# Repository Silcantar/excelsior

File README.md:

# *Excelsior*
>
>Tentative layout and design for *Excelsior*.

*Excelsior* is a 150% (153 keys) 3-section hand-wired keyboard (optionally) using uniform keycaps in a curved plate.

The main section is based on a standard ANSI 60% keyboard, but with a row of 15 function/programmable-macro keys at the top and 5 keys below the 7u spacebar.

The peripheral sections are each 6x6 ortholinear boards and can be placed on either side of the main section, including placing both on the same side of the main. They are connected to the main section by 20-pin pogo pin connectors either directly or via a custom cable. In the default keymap one section is an extended numpad and the other is a large navigation/macro pad. The top row of each peripheral is dedicated to additional function/programmable-macro keys for a total of 27.

The microcontroller is a Pimoroni PGA2350 board located in the main section. The matrix for the main section is wired directly to the controller board, while the I/O for the peripheral sections is handled by an MCP23017 I/O expander in each section communicating with the controller via I²C. The connections between the sections carry the signals necessary for both I²C and for SPI, plus several spare lines for interrupts, chip selects, or other I/O.

The matrix of the main section also has a seventh row that can be used for up to 14 momentary, toggle, or rotary switches on the top bezel of the keyboard. Note that the keys below the spacebar are on the sixth (spacebar) row of the matrix, so the seventh row is completely open.

Because of the massive number of GPIO pins on the PGA2350 and the I/O expanders, there is ample spare I/O for any functionality you could possibly want, from displays, encoders, LEDs, etc.

Because QMK does not currently support the RP2350 or displays larger than 128×64, I am planning to use KMK for the firmware.

For those interested, I have designed a [custom set](https://yuzukeycaps.com/c/4633754e-42e4-428c-9306-6221ce11477c)[^1] of KAM keycaps with a white-on-black-with-blue-accents *Wall Street Journal*-inspired aesthetic for *Excelsior* at YUZU Keycaps. They also feature secondary legends for a Greek alphabet/symbol layer and the macro keys are labeled with Greek numerals. There are a number of extra keys for alternative layouts too. Since the keycaps have a uniform profile any key can be placed on any row.

[^1]: If the link does not work, you can import [this JSON file](keycaps/Excelsior.json) to YUZU

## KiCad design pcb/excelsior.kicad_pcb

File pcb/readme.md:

This is a hand-wired build, so the "PCBs" here are not meant for production. I am using them to select and record the necessary components and to verify that the wiring topology is feasible.

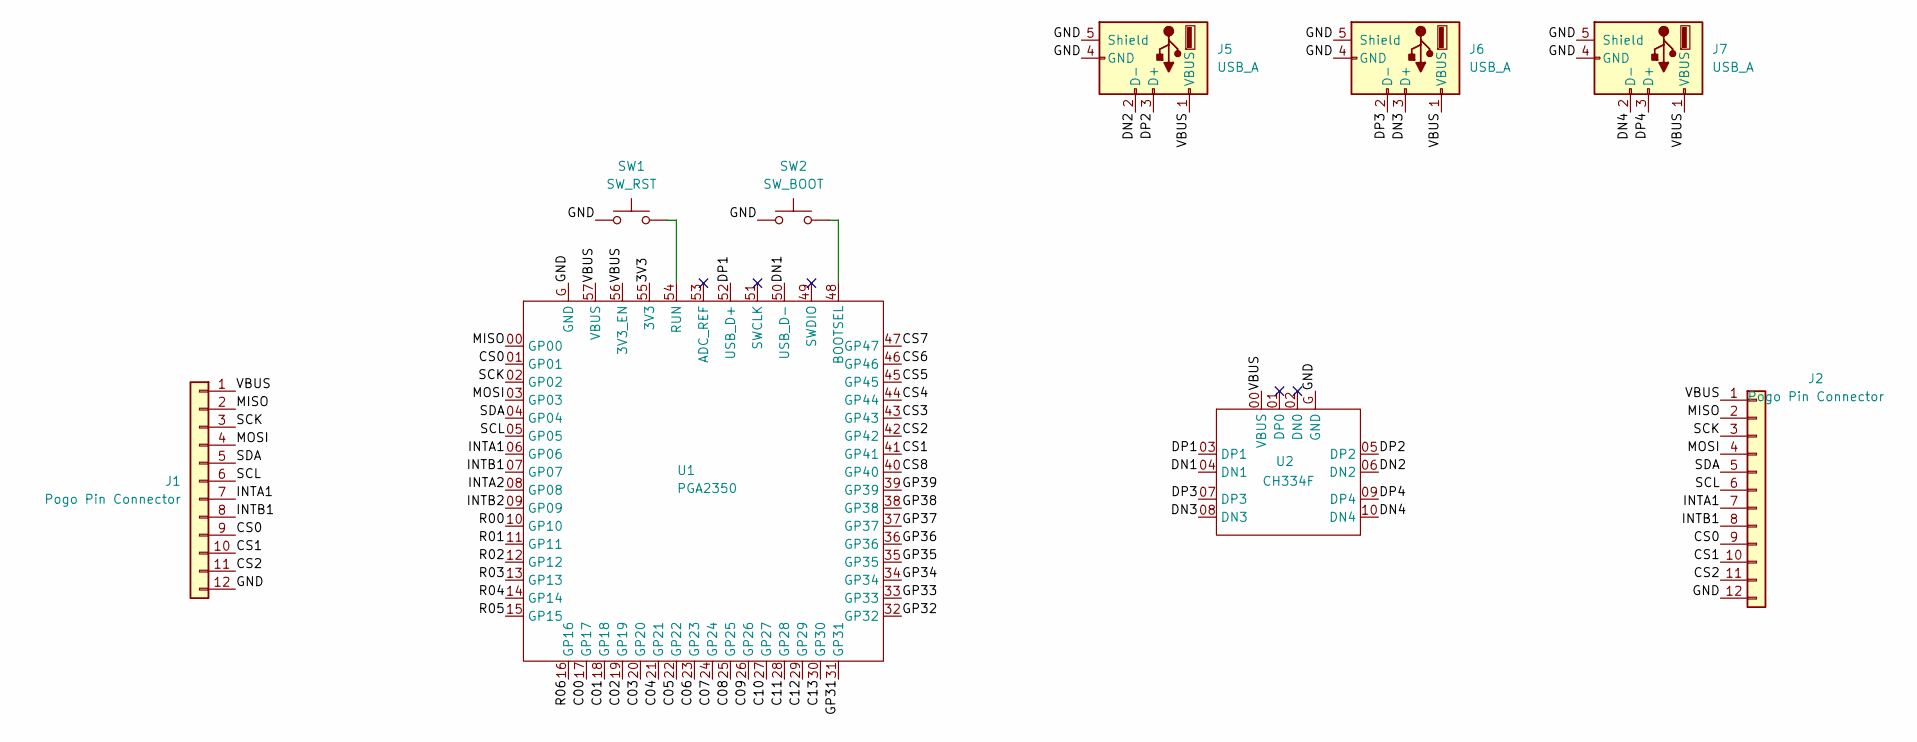
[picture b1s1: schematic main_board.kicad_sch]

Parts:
J1, J2: Pogo Pin Connector; PinHeader_1x12_P2.54mm_Vertical
J5, J6, J7: USB_A; USB_A_Molex_67643_Horizontal
SW1: SW_RST; SW_PUSH_6mm
SW2: SW_BOOT; SW_PUSH_6mm
U1: PGA2350
U2: CH334F; USB_Hub

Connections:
/Main Board/3V3: U1.55 (3V3)
/Main Board/C00: U1.17 (GP17)
/Main Board/C01: U1.18 (GP18)
/Main Board/C02: U1.19 (GP19)
/Main Board/C03: U1.20 (GP20)
/Main Board/C04: U1.21 (GP21)
/Main Board/C05: U1.22 (GP22)
/Main Board/C06: U1.23 (GP23)
/Main Board/C07: U1.24 (GP24)
/Main Board/C08: U1.25 (GP25)
/Main Board/C09: U1.26 (GP26)
/Main Board/C10: U1.27 (GP27)
/Main Board/C11: U1.28 (GP28)
/Main Board/C12: U1.29 (GP29)
/Main Board/C13: U1.30 (GP30)
/Main Board/CS0: J1.9, J2.9, U1.01 (GP01)
/Main Board/CS1: J1.10, J2.10, U1.41 (GP41)
/Main Board/CS2: J1.11, J2.11, U1.42 (GP42)
/Main Board/CS3: U1.43 (GP43)
/Main Board/CS4: U1.44 (GP44)
/Main Board/CS5: U1.45 (GP45)
/Main Board/CS6: U1.46 (GP46)
/Main Board/CS7: U1.47 (GP47)
/Main Board/CS8: U1.40 (GP40)
/Main Board/DN1: U1.50 (USB_D-), U2.04 (DN1)
/Main Board/DN2: J5.2 (D-), U2.06 (DN2)
/Main Board/DN3: J6.3 (D+), U2.08 (DN3)
/Main Board/DN4: J7.2 (D-), U2.10 (DN4)
/Main Board/DP1: U1.52 (USB_D+), U2.03 (DP1)
/Main Board/DP2: J5.3 (D+), U2.05 (DP2)
/Main Board/DP3: J6.2 (D-), U2.07 (DP3)
/Main Board/DP4: J7.3 (D+), U2.09 (DP4)
/Main Board/GND: J1.12, J2.12, J5.4 (GND), J5.5 (Shield), J6.4 (GND), J6.5 (Shield), J7.4 (GND), J7.5 (Shield), SW1.1, SW2.1, U1.G (GND), U2.G (GND)
/Main Board/GP31: U1.31 (GP31)
/Main Board/GP32: U1.32 (GP32)
/Main Board/GP33: U1.33 (GP33)
/Main Board/GP34: U1.34 (GP34)
/Main Board/GP35: U1.35 (GP35)
/Main Board/GP36: U1.36 (GP36)
/Main Board/GP37: U1.37 (GP37)
/Main Board/GP38: U1.38 (GP38)
/Main Board/GP39: U1.39 (GP39)
/Main Board/INTA1: J1.7, J2.7, U1.06 (GP06)
/Main Board/INTA2: U1.08 (GP08)
/Main Board/INTB1: J1.8, J2.8, U1.07 (GP07)
/Main Board/INTB2: U1.09 (GP09)
/Main Board/MISO: J1.2, J2.2, U1.00 (GP00)
/Main Board/MOSI: J1.4, J2.4, U1.03 (GP03)
/Main Board/R00: U1.10 (GP10)
/Main Board/R01: U1.11 (GP11)
/Main Board/R02: U1.12 (GP12)
/Main Board/R03: U1.13 (GP13)
/Main Board/R04: U1.14 (GP14)
/Main Board/R05: U1.15 (GP15)
/Main Board/R06: U1.16 (GP16)
/Main Board/SCK: J1.3, J2.3, U1.02 (GP02)
/Main Board/SCL: J1.6, J2.6, U1.05 (GP05)
/Main Board/SDA: J1.5, J2.5, U1.04 (GP04)
/Main Board/VBUS: J1.1, J2.1, J5.1 (VBUS), J6.1 (VBUS), J7.1 (VBUS), U1.56 (3V3_EN), U1.57 (VBUS), U2.00 (VBUS)
unnamed: SW2.2, U1.48 (BOOTSEL)
unnamed: SW1.2, U1.54 (RUN)

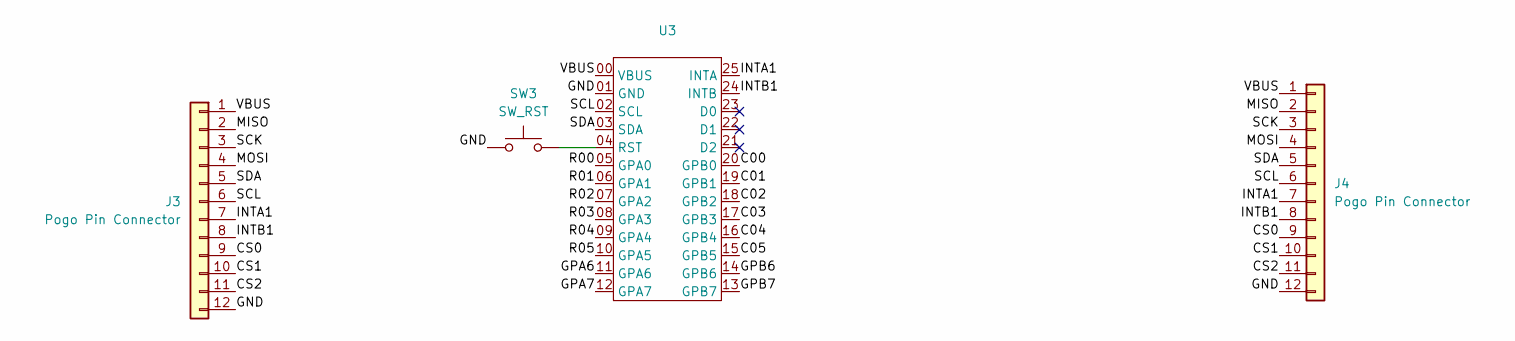
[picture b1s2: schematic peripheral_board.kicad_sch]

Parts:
J3, J4: Pogo Pin Connector; PinHeader_1x12_P2.54mm_Vertical
SW3: SW_RST; SW_PUSH_6mm
U3: MCP23017_Breakout

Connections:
/Peripheral Board/C00: U3.20 (GPB0)
/Peripheral Board/C01: U3.19 (GPB1)
/Peripheral Board/C02: U3.18 (GPB2)
/Peripheral Board/C03: U3.17 (GPB3)
/Peripheral Board/C04: U3.16 (GPB4)
/Peripheral Board/C05: U3.15 (GPB5)
/Peripheral Board/CS0: J3.9, J4.9
/Peripheral Board/CS1: J3.10, J4.10
/Peripheral Board/CS2: J3.11, J4.11
/Peripheral Board/GND: J3.12, J4.12, SW3.1, U3.01 (GND)
/Peripheral Board/GPA6: U3.11 (GPA6)
/Peripheral Board/GPA7: U3.12 (GPA7)
/Peripheral Board/GPB6: U3.14 (GPB6)
/Peripheral Board/GPB7: U3.13 (GPB7)
/Peripheral Board/INTA1: J3.7, J4.7, U3.25 (INTA)
/Peripheral Board/INTB1: J3.8, J4.8, U3.24 (INTB)
/Peripheral Board/MISO: J3.2, J4.2
/Peripheral Board/MOSI: J3.4, J4.4
/Peripheral Board/R00: U3.05 (GPA0)
/Peripheral Board/R01: U3.06 (GPA1)
/Peripheral Board/R02: U3.07 (GPA2)
/Peripheral Board/R03: U3.08 (GPA3)
/Peripheral Board/R04: U3.09 (GPA4)
/Peripheral Board/R05: U3.10 (GPA5)
/Peripheral Board/SCK: J3.3, J4.3
/Peripheral Board/SCL: J3.6, J4.6, U3.02 (SCL)
/Peripheral Board/SDA: J3.5, J4.5, U3.03 (SDA)
/Peripheral Board/VBUS: J3.1, J4.1, U3.00 (VBUS)
unnamed: SW3.2, U3.04 (RST)

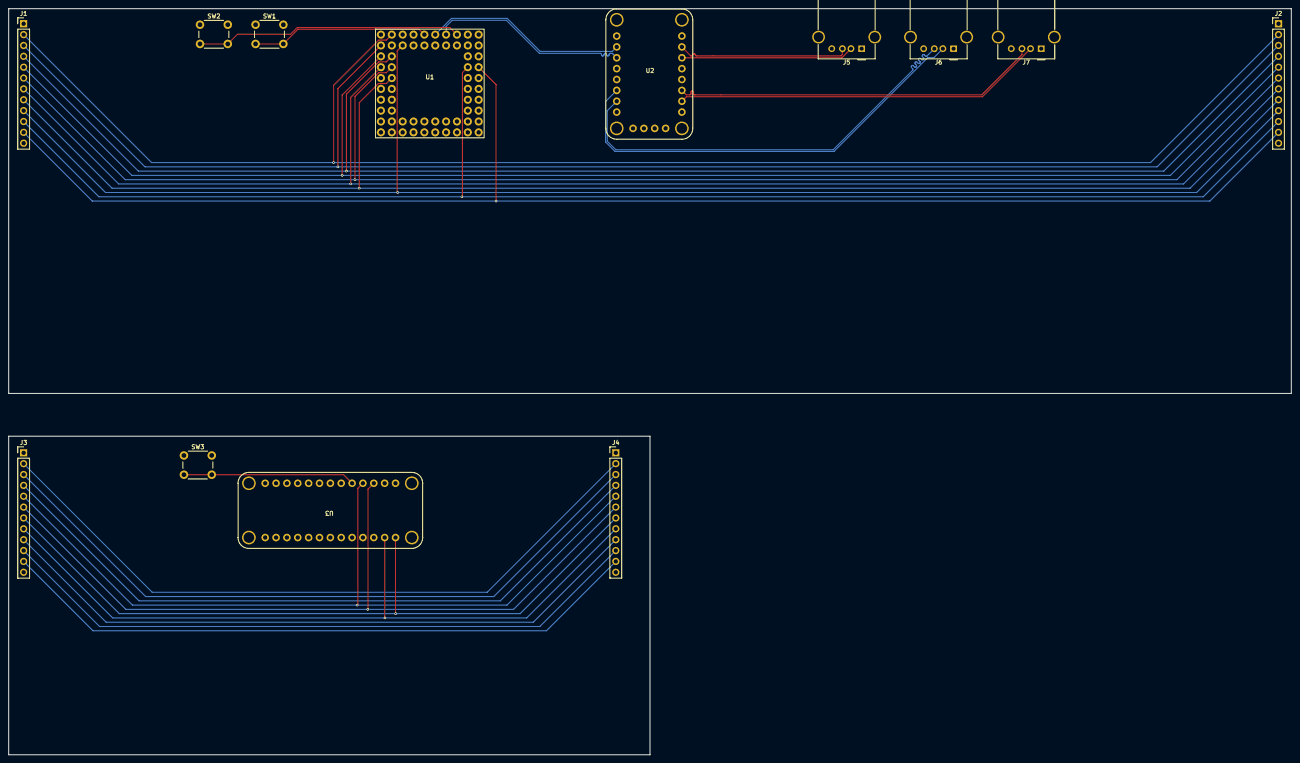
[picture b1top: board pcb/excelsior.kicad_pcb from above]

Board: 4 copper layers, 300.0 x 174.5 mm, 13 parts (0 on the bottom side), 35 nets.

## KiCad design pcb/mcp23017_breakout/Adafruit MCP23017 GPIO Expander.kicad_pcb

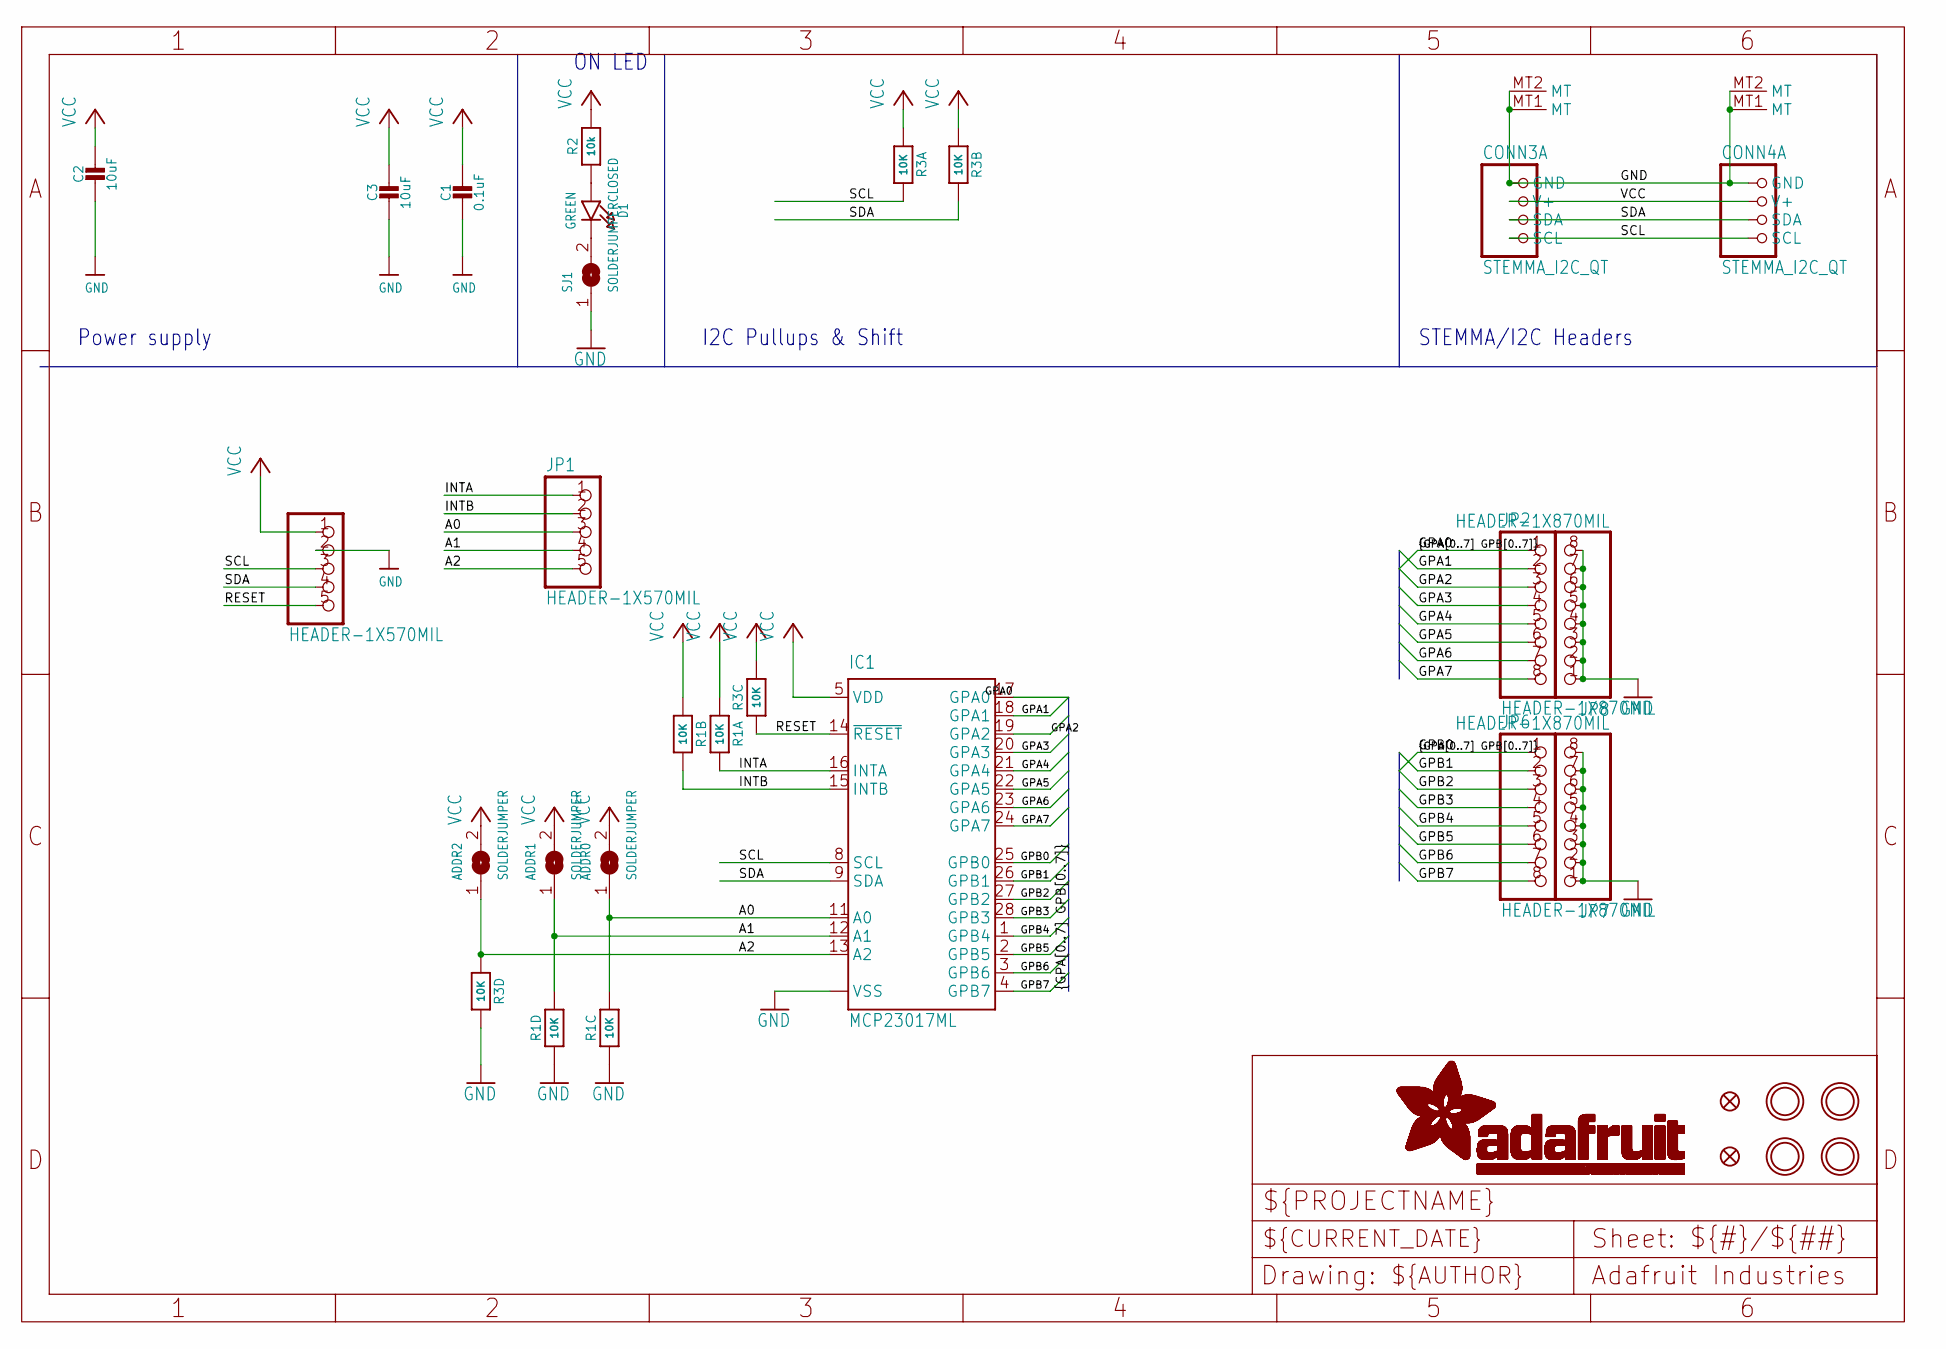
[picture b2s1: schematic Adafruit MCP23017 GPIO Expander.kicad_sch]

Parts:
ADDR0, ADDR1, ADDR2: SOLDERJUMPER; SOLDERJUMPER_ARROW_NOPASTE
C1: 0.1uF; 0603-NO
C2, C3: 10uF; 0805-NO
CONN3, CONN4: STEMMA_I2C_QT; JST_SH4
D1: GREEN; CHIPLED_0603_NOOUTLINE
FID3, FID4: FIDUCIAL_1MM
IC1: MCP23017ML; QFN28-ML_6X6MM
JP1, JP5: HEADER-1X570MIL; 1X05_ROUND_70
JP2, JP6, JP7, JP8: HEADER-1X870MIL; 1X08_ROUND_70
R1, R3: 10K; RESPACK_4X0603
R2: 10k; 0603-NO
SJ1: SOLDERJUMPERCLOSED; SOLDERJUMPER_CLOSEDWIRE
U$1, U$17, U$19, U$21: MOUNTINGHOLE2.5; MOUNTINGHOLE_2.5_PLATED

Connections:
A0: ADDR0.1, IC1.11 (A0), JP1.3, R1.6 (2)
A1: ADDR1.1, IC1.12 (A1), JP1.4, R1.5 (2)
A2: ADDR2.1, IC1.13 (A2), JP1.5, R3.4 (1)
GND: C1.2, C2.2, C3.2, CONN3.1 (GND), CONN3.MT1 (MT), CONN3.MT2 (MT), CONN4.1 (GND), CONN4.MT1 (MT), CONN4.MT2 (MT), IC1.6 (VSS), IC1.EXP (VSS), JP5.2, JP7.1, JP7.2, JP7.3, JP7.4, JP7.5, JP7.6, JP7.7, JP7.8, JP8.1, JP8.2, JP8.3, JP8.4, JP8.5, JP8.6, JP8.7, JP8.8, R1.3 (1), R1.4 (1), R3.5 (2), SJ1.1
GPA1: IC1.18 (GPA1), JP2.2
GPA2: IC1.19 (GPA2), JP2.3
GPA3: IC1.20 (GPA3), JP2.4
GPA4: IC1.21 (GPA4), JP2.5
GPA5: IC1.22 (GPA5), JP2.6
GPA6: IC1.23 (GPA6), JP2.7
GPA7: IC1.24 (GPA7), JP2.8
GPB1: IC1.26 (GPB1), JP6.2
GPB2: IC1.27 (GPB2), JP6.3
GPB3: IC1.28 (GPB3), JP6.4
GPB4: IC1.1 (GPB4), JP6.5
GPB5: IC1.2 (GPB5), JP6.6
GPB6: IC1.3 (GPB6), JP6.7
GPB7: IC1.4 (GPB7), JP6.8
INTA: IC1.16 (INTA), JP1.1, R1.8 (2)
INTB: IC1.15 (INTB), JP1.2, R1.7 (2)
unnamed: D1.A, R2.1
unnamed: D1.C, SJ1.2
RESET: IC1.14 (~RESET), JP5.5, R3.3 (1)
SCL: CONN3.4 (SCL), CONN4.4 (SCL), IC1.8 (SCL), JP5.3, R3.8 (2)
SDA: CONN3.3 (SDA), CONN4.3 (SDA), IC1.9 (SDA), JP5.4, R3.7 (2)
VCC: ADDR0.2, ADDR1.2, ADDR2.2, C1.1, C2.1, C3.1, CONN3.2 (V+), CONN4.2 (V+), IC1.5 (VDD), JP5.1, R1.1, R1.2 (1), R2.2, R3.1, R3.2 (1), R3.6 (2)

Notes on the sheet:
ON LED
Power supply
I2C Pullups & Shift
STEMMA/I2C Headers

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
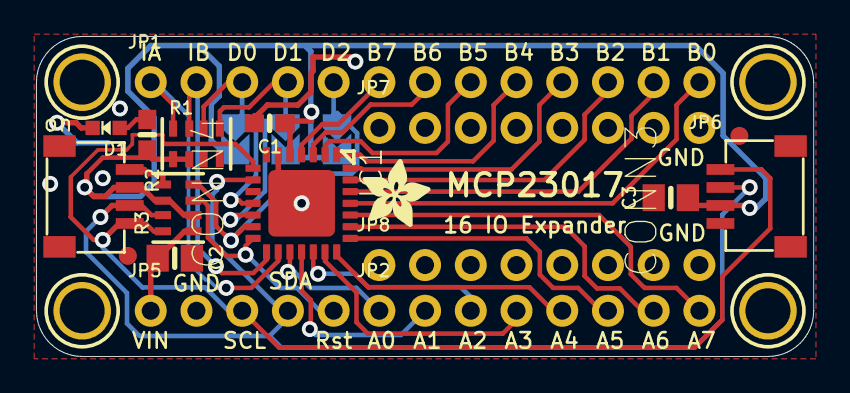
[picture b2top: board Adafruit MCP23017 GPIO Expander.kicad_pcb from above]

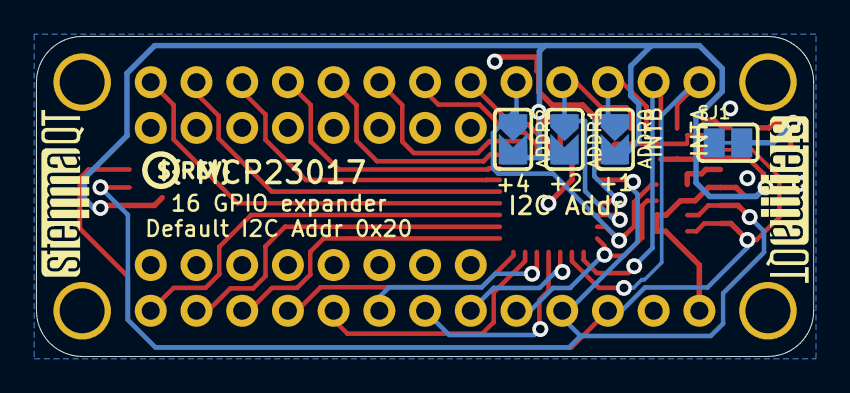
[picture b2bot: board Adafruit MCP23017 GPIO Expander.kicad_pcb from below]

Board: 2 copper layers, 43.2 x 17.8 mm, 30 parts (7 on the bottom side), 28 nets.

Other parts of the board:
U$22: ADAFRUIT_3.5MM
U$25: PCBFEAT-REV-040
U$30, U$31: STEMMAQT

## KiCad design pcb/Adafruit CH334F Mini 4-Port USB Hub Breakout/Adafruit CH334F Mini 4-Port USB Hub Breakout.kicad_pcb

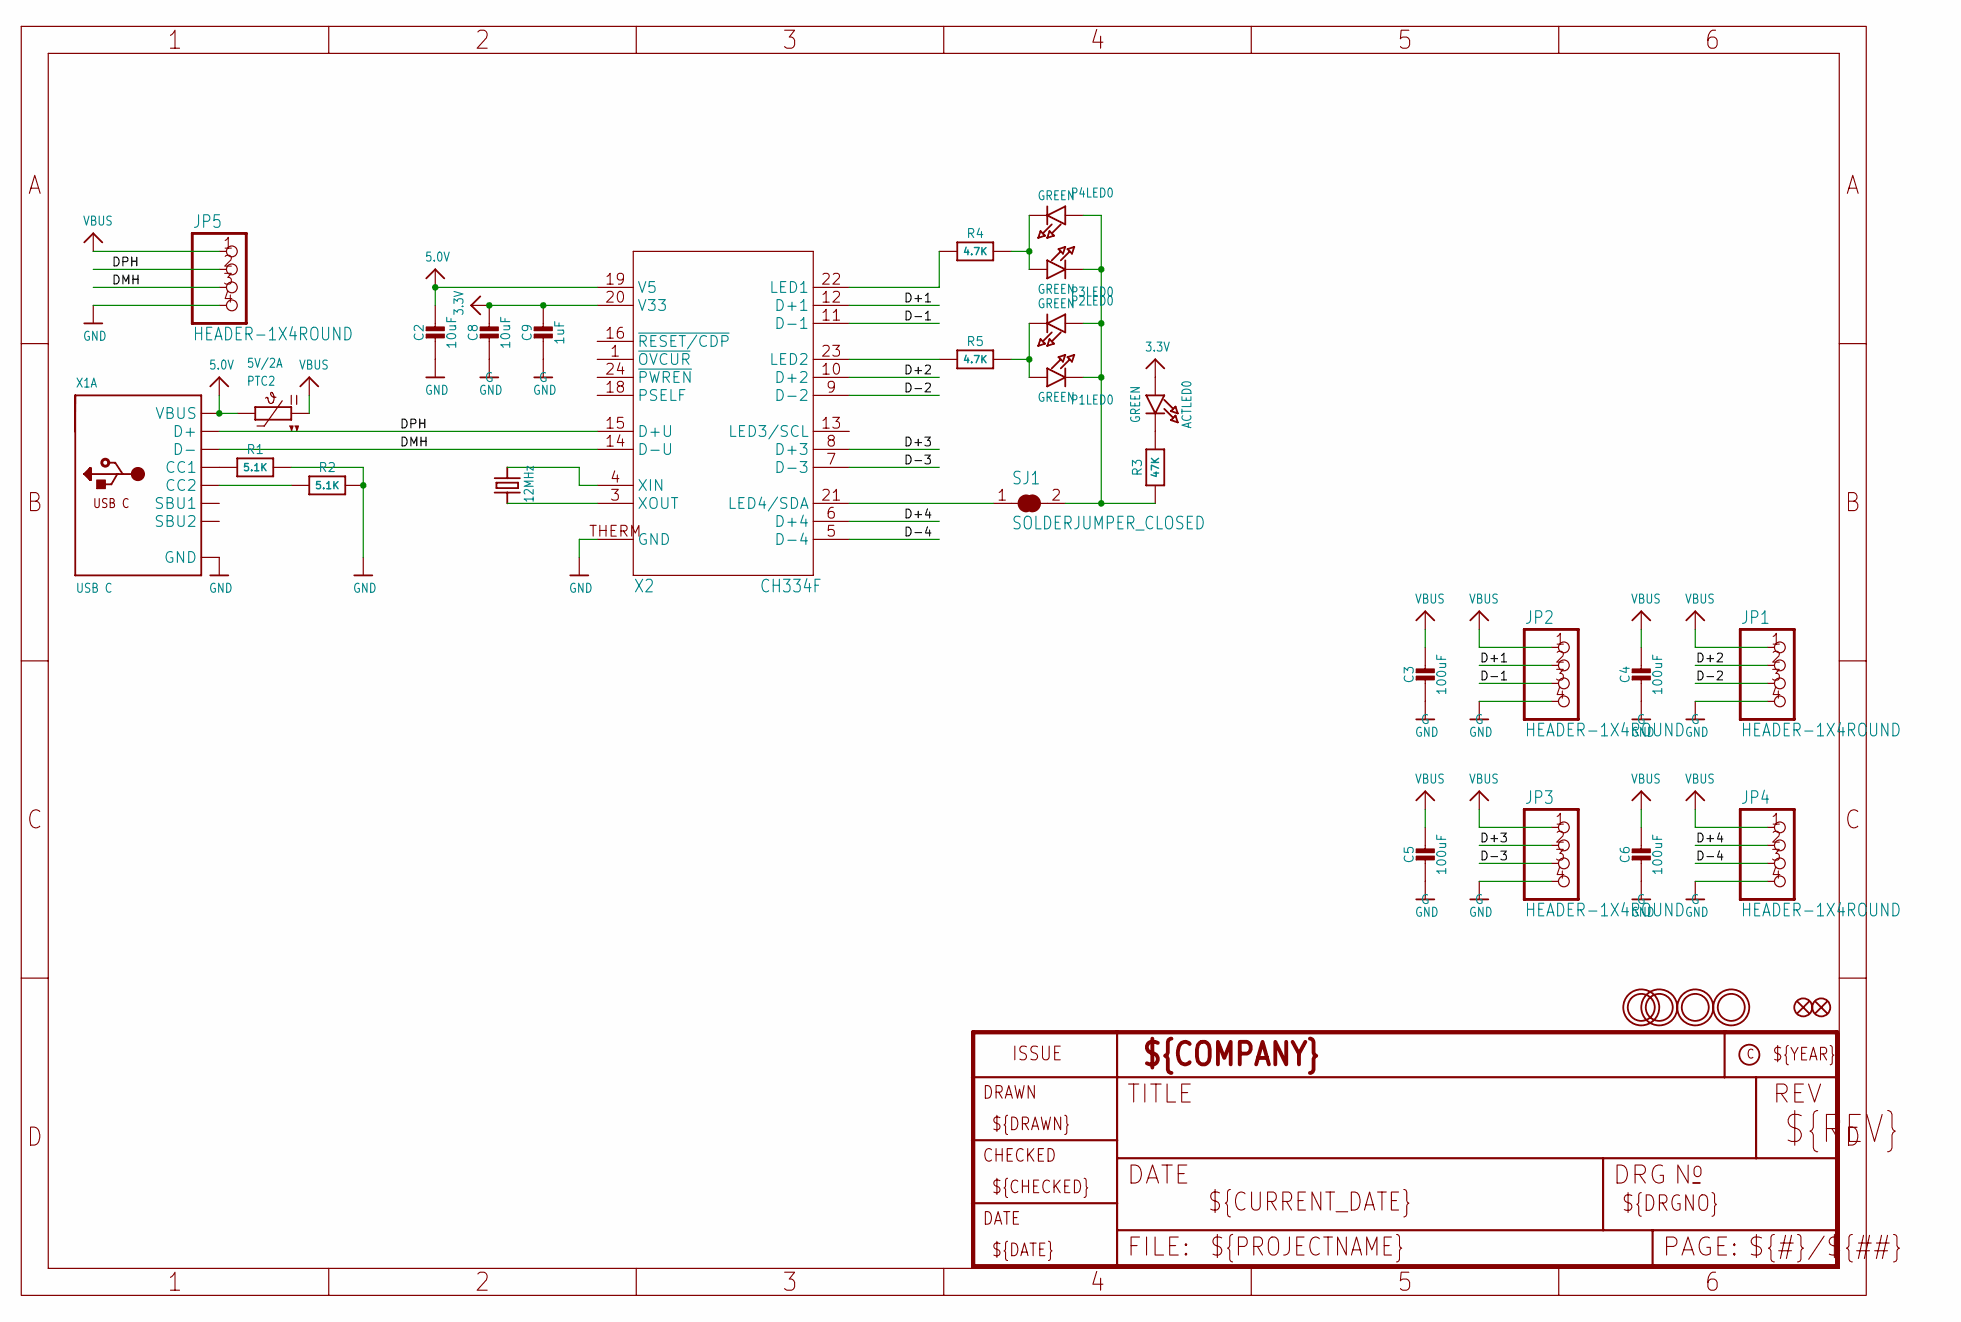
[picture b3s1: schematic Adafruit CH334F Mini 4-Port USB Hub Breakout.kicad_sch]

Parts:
ACTLED0: GREEN; CHIPLED_0603_NOOUTLINE
C2, C8: 10uF; 0805-NO
C3, C4, C5, C6: 100uF; _1206
C9: 1uF; 0603-NO
FID1, FID2: FIDUCIAL_0.5MM
JP1, JP2, JP3, JP4, JP5: HEADER-1X4ROUND; 1X04_ROUND
P1LED0, P2LED0, P3LED0, P4LED0: GREEN; CHIPLED_0603_NOOUTLINE
PTC2: 5V/2A; 0805-NO
R1, R2: 5.1K; 0603-NO
R3: 47K; 0603-NO
R4, R5: 4.7K; 0603-NO
SJ1: SOLDERJUMPER_CLOSED; SOLDERJUMPER_CLOSEDWIRE
U$23, U$28, U$29, U$31: MOUNTINGHOLE2.5; MOUNTINGHOLE_2.5_PLATED
X1: USB C; USB_C_CUSB31-CFM2AX-01-X
X2: CH334F; QFN24_4MM
Y1: 12MHz; CRYSTAL_2.5X2

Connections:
3.3V: ACTLED0.A, C8.1, C9.1, X2.20 (V33)
5.0V: C2.1, PTC2.2, X1.A4B9 (VBUS), X1.B4A9 (VBUS), X2.19 (V5)
D+1: JP2.2, X2.12 (D+1)
D+2: JP1.2, X2.10 (D+2)
D+3: JP3.2, X2.8 (D+3)
D+4: JP4.2, X2.6 (D+4)
D-1: JP2.3, X2.11 (D-1)
D-2: JP1.3, X2.9 (D-2)
D-3: JP3.3, X2.7 (D-3)
D-4: JP4.3, X2.5 (D-4)
DMH: JP5.3, X1.A7 (D-), X1.B7 (D-), X2.14 (D-U)
DPH: JP5.2, X1.A6 (D+), X1.B6 (D+), X2.15 (D+U)
GND: C2.2, C3.2, C4.2, C5.2, C6.2, C8.2, C9.2, JP1.4, JP2.4, JP3.4, JP4.4, JP5.4, R1.2, R2.2, X1.A1B12 (GND), X1.B1A12 (GND), X2.THERM (GND)
unnamed: R1.1, X1.A5 (CC1)
unnamed: R2.1, X1.B5 (CC2)
unnamed: X2.3 (XOUT), Y1.1
unnamed: X2.4 (XIN), Y1.3 (2)
unnamed: ACTLED0.C, R3.2
unnamed: P1LED0.C, P2LED0.A, P3LED0.C, P4LED0.A, R3.1, SJ1.2
unnamed: P3LED0.A, P4LED0.C, R4.2
unnamed: R4.1, X2.22 (LED1)
unnamed: SJ1.1, X2.21 (LED4/SDA)
unnamed: P1LED0.A, P2LED0.C, R5.2
unnamed: R5.1, X2.23 (LED2)
VBUS: C3.1, C4.1, C5.1, C6.1, JP1.1, JP2.1, JP3.1, JP4.1, JP5.1, PTC2.1

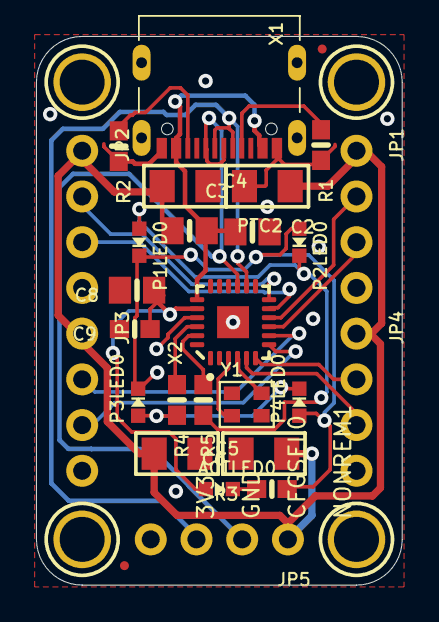
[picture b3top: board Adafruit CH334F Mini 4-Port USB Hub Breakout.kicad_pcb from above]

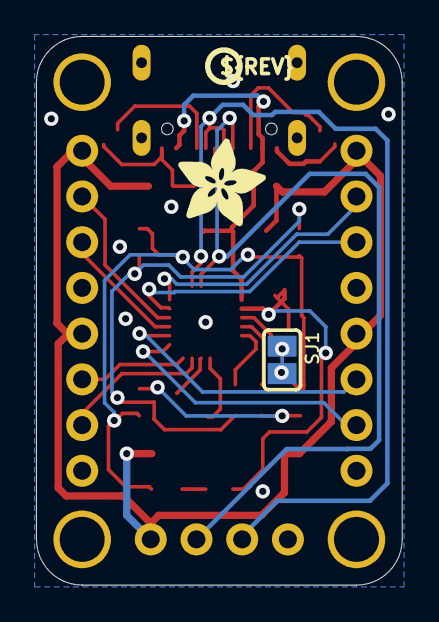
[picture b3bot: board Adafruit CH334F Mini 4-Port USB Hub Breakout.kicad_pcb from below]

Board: 2 copper layers, 20.3 x 30.5 mm, 68 parts (11 on the bottom side), 25 nets.

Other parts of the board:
PLABEL0: PLABEL0
PLABEL1: PLABEL1
PLABEL2: PLABEL2
PLABEL3: PLABEL3
PLABEL4: PLABEL4
PLABEL5: PLABEL5
PLABEL6: PLABEL6
PLABEL7: PLABEL7
PLABEL8: PLABEL8
PLABEL9: PLABEL9
PLABEL10: PLABEL10
PLABEL11: PLABEL11
PLABEL12: PLABEL12
PLABEL13: PLABEL13
PLABEL14: PLABEL14
PLABEL15: PLABEL15
PLABEL16: PLABEL16
PLABEL17: PLABEL17
PLABEL18: PLABEL18
PLABEL19: PLABEL19
PLABEL20: PLABEL20
PLABEL21: PLABEL21
PLABEL22: PLABEL22
PLABEL23: PLABEL23
PLABEL24: PLABEL24
PLABEL25: PLABEL25
PLABEL26: PLABEL26
PLABEL27: PLABEL27
PLABEL28: PLABEL28
PLABEL29: PLABEL29
PLABEL30: PLABEL30
PLABEL31: PLABEL31
PLABEL32: PLABEL32
U$33: ADAFRUIT_5MM
U$34: PCBFEAT-REV-040

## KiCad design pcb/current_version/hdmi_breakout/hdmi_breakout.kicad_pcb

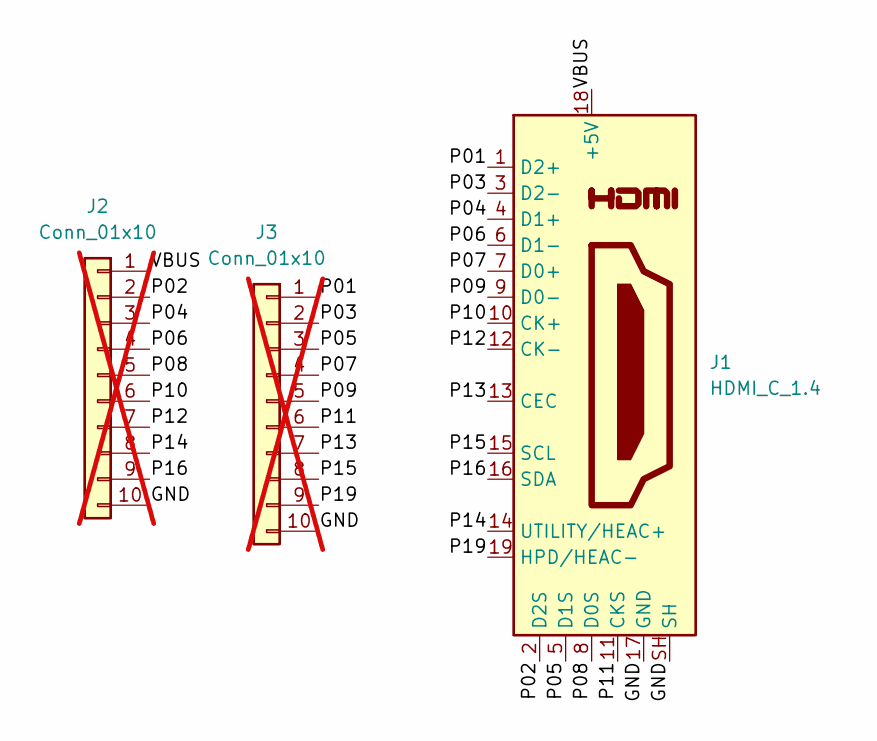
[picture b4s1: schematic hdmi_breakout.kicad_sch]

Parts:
J1: HDMI_C_1.4; HDMI_A_Molex_208658-1001_Horizontal
J2, J3: Conn_01x10; PinHeader_1x10_P2.54mm_Vertical; not fitted

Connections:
/GND: J1.17 (GND), J1.SH, J2.10, J3.10
/P01: J1.1 (D2+), J3.1
/P02: J1.2 (D2S), J2.2
/P03: J1.3 (D2-), J3.2
/P04: J1.4 (D1+), J2.3
/P05: J1.5 (D1S), J3.3
/P06: J1.6 (D1-), J2.4
/P07: J1.7 (D0+), J3.4
/P08: J1.8 (D0S), J2.5
/P09: J1.9 (D0-), J3.5
/P10: J1.10 (CK+), J2.6
/P11: J1.11 (CKS), J3.6
/P12: J1.12 (CK-), J2.7
/P13: J1.13 (CEC), J3.7
/P14: J1.14 (UTILITY/HEAC+), J2.8
/P15: J1.15 (SCL), J3.8
/P16: J1.16 (SDA), J2.9
/P19: J1.19 (HPD/HEAC-), J3.9
/VBUS: J1.18 (+5V), J2.1

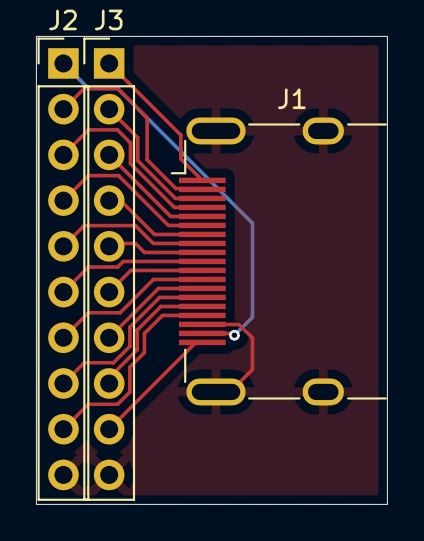
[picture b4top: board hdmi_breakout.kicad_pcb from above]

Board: 2 copper layers, 19.5 x 26.0 mm, 3 parts (0 on the bottom side), 19 nets.

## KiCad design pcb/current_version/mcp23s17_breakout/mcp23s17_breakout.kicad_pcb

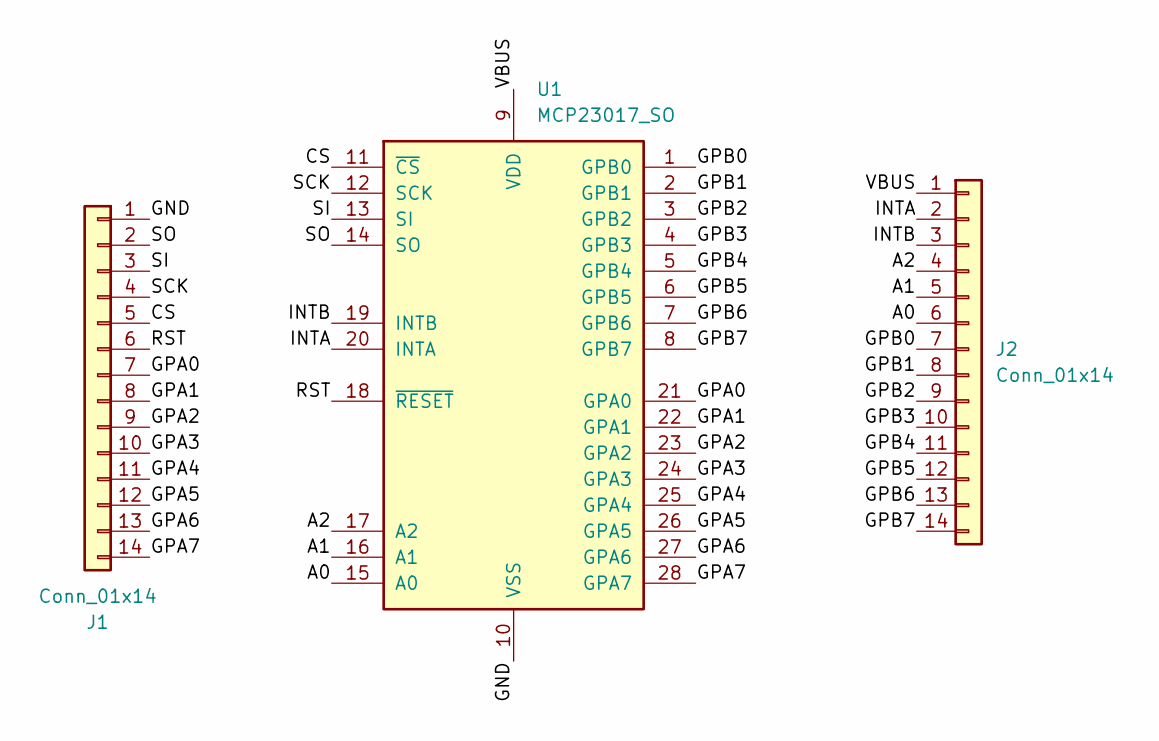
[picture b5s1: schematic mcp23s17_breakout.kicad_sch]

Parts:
J1, J2: Conn_01x14; PinHeader_1x14_P2.54mm_Vertical
U1: MCP23017_SO; SOIC-28W_7.5x17.9mm_P1.27mm

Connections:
/A0: J2.6, U1.15 (A0)
/A1: J2.5, U1.16 (A1)
/A2: J2.4, U1.17 (A2)
/CS: J1.5, U1.11 (~CS)
/GND: J1.1, U1.10 (VSS)
/GPA0: J1.7, U1.21 (GPA0)
/GPA1: J1.8, U1.22 (GPA1)
/GPA2: J1.9, U1.23 (GPA2)
/GPA3: J1.10, U1.24 (GPA3)
/GPA4: J1.11, U1.25 (GPA4)
/GPA5: J1.12, U1.26 (GPA5)
/GPA6: J1.13, U1.27 (GPA6)
/GPA7: J1.14, U1.28 (GPA7)
/GPB0: J2.7, U1.1 (GPB0)
/GPB1: J2.8, U1.2 (GPB1)
/GPB2: J2.9, U1.3 (GPB2)
/GPB3: J2.10, U1.4 (GPB3)
/GPB4: J2.11, U1.5 (GPB4)
/GPB5: J2.12, U1.6 (GPB5)
/GPB6: J2.13, U1.7 (GPB6)
/GPB7: J2.14, U1.8 (GPB7)
/INTA: J2.2, U1.20 (INTA)
/INTB: J2.3, U1.19 (INTB)
/RST: J1.6, U1.18 (~RESET)
/SCK: J1.4, U1.12 (SCK)
/SI: J1.3, U1.13 (SI)
/SO: J1.2, U1.14 (SO)
/VBUS: J2.1, U1.9 (VDD)

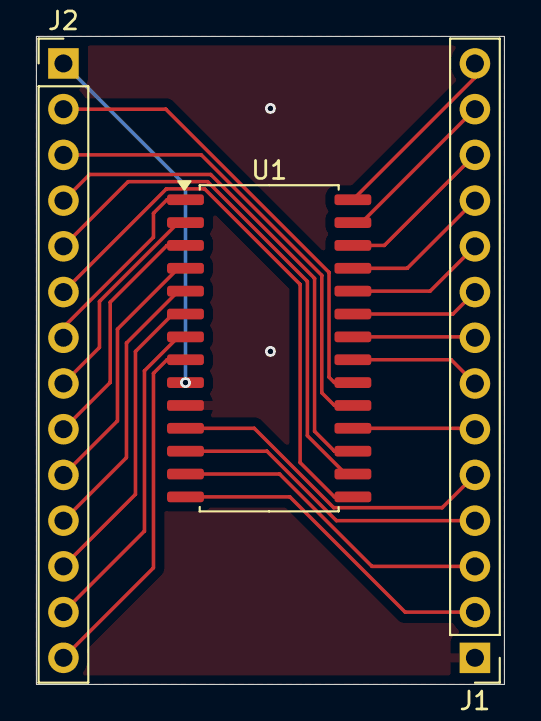
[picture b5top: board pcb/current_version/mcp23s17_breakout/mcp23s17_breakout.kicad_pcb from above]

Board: 2 copper layers, 26.0 x 36.0 mm, 3 parts (0 on the bottom side), 28 nets.

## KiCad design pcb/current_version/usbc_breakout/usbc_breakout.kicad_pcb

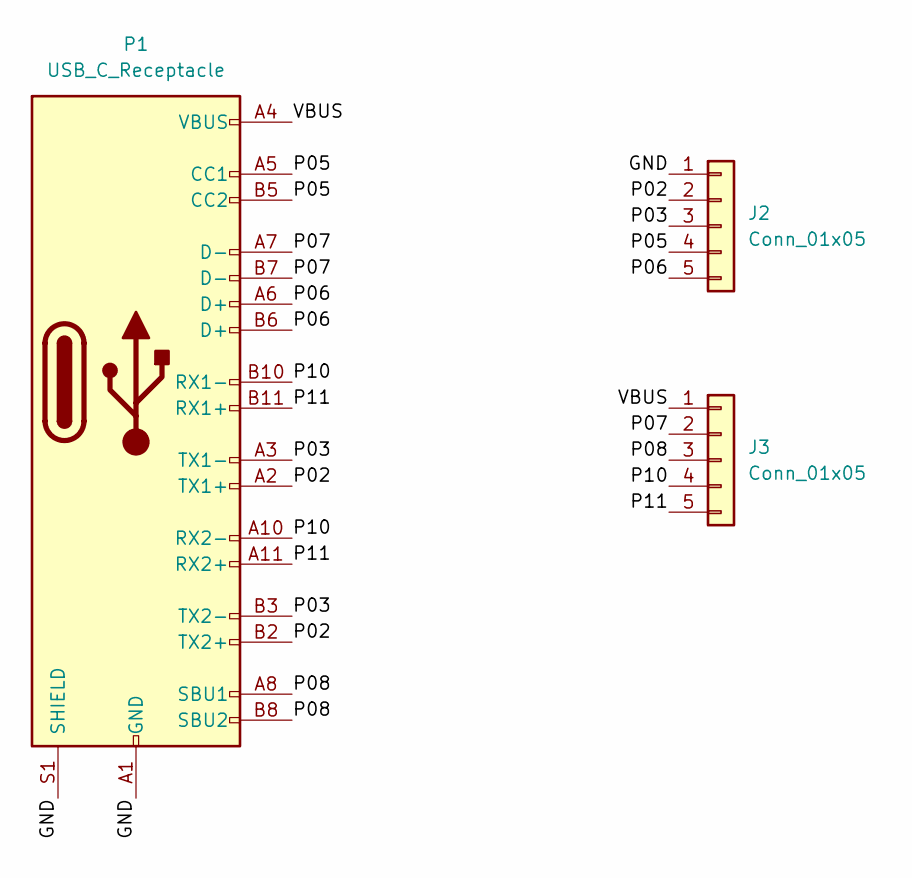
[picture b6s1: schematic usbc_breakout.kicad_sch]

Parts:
J2, J3: Conn_01x05; PinHeader_1x05_P2.54mm_Vertical
P1: USB_C_Receptacle; USB_C_Receptacle_JAE_DX07S024WJ3R400

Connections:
/GND: J2.1, P1.A1 (GND), P1.A12 (GND), P1.B1 (GND), P1.B12 (GND), P1.S1 (SHIELD)
/P02: J2.2, P1.A2 (TX1+), P1.B2 (TX2+)
/P03: J2.3, P1.A3 (TX1-), P1.B3 (TX2-)
/P05: J2.4, P1.A5 (CC1), P1.B5 (CC2)
/P06: J2.5, P1.A6 (D+), P1.B6 (D+)
/P07: J3.2, P1.A7 (D-), P1.B7 (D-)
/P08: J3.3, P1.A8 (SBU1), P1.B8 (SBU2)
/P10: J3.4, P1.A10 (RX2-), P1.B10 (RX1-)
/P11: J3.5, P1.A11 (RX2+), P1.B11 (RX1+)
/VBUS: J3.1, P1.A4 (VBUS), P1.A9 (VBUS), P1.B4 (VBUS), P1.B9 (VBUS)

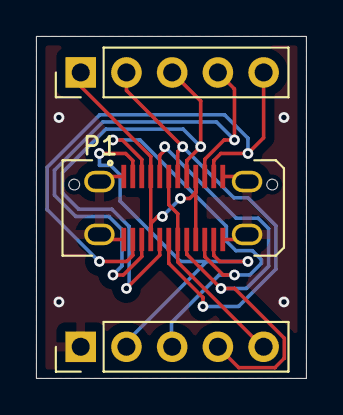
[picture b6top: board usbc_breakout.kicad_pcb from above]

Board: 2 copper layers, 15.0 x 19.0 mm, 3 parts (0 on the bottom side), 10 nets.
